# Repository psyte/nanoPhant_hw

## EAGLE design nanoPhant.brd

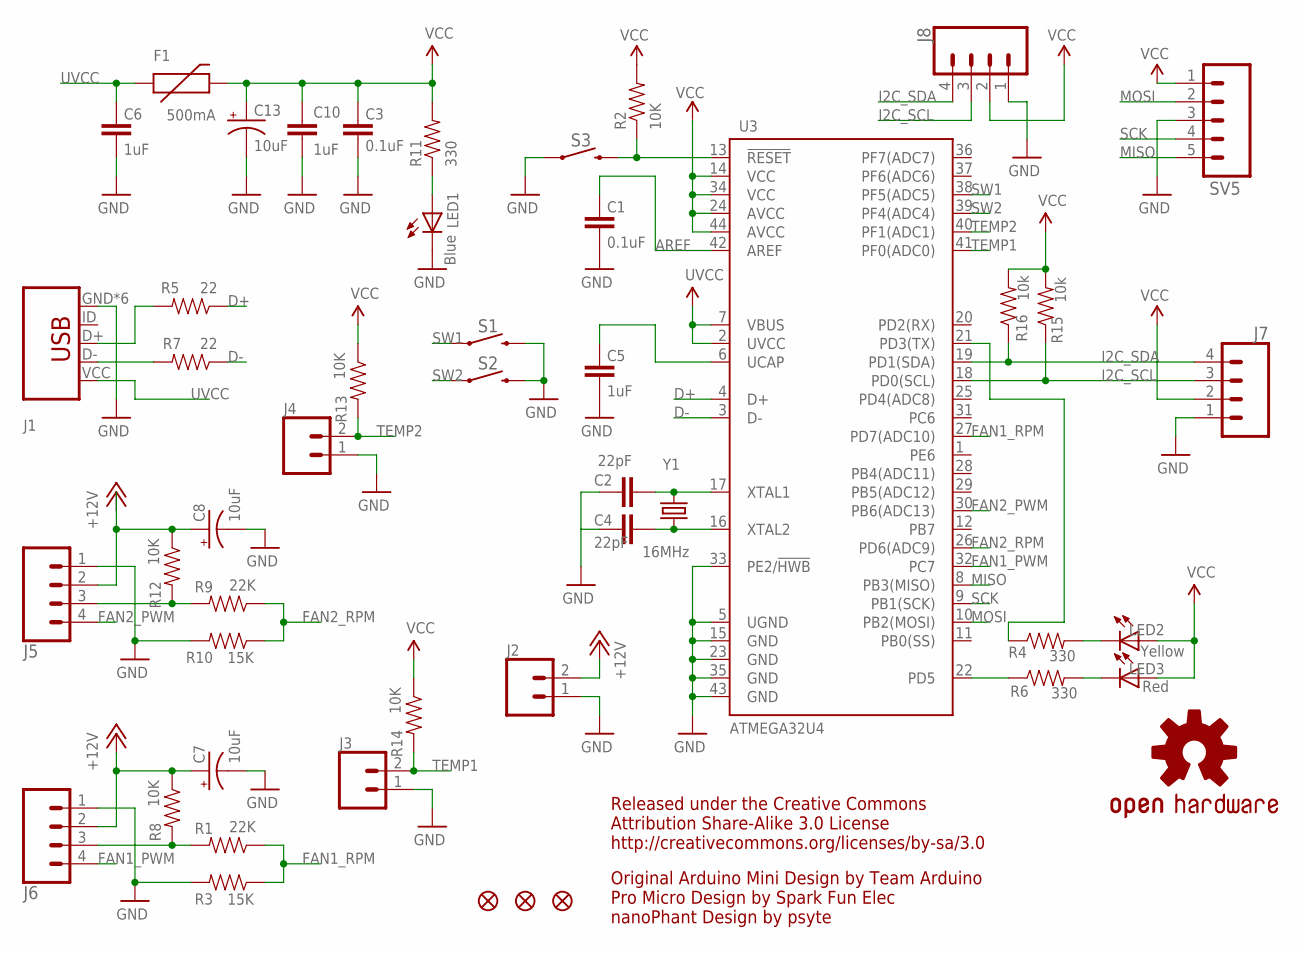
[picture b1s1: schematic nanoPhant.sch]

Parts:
C1, C3: 0.1uF; C0603
C2, C4: 22pF; C0603
C5, C6, C10: 1uF; C0603
C7, C8, C13: 10uF; EIA3216
F1: 500mA; PTC-1206
FD1, FD2, FD3: FIDUCIAL1X2; FIDUCIAL-1X2
J1: AMP FCI 10103594-0001LF; MICRO_USB_4_LEGS
J2, J3, J4: CONN_02; 1X02
J5, J6, J7, J8: CONN_04; 1X04
LED1: Blue; LED-0603
LED2: Yellow; LED-0603
LED3: Red; LED-0603
R1, R9: 22K; 0603-RES
R2, R8, R12, R13, R14: 10K; 0603-RES
R3, R10: 15K; 0603-RES
R4, R6, R11: 330; 0603-RES
R5, R7: 22; 0603-RES
R15, R16: 10k; 0603-RES
S1, S2, S3: MOMENTARY-SWITCH-SPST-SMD-6.0X3.5MM; TACTILE_SWITCH_SMD_6.0X3.5MM
SV5: CONN_05; 1X05
U3: ATMEGA32U4; QFN-44-NOPAD_1:1-OUTFAKES
U$3: OSHW-LOGOS; OSHW-LOGO-S
Y1: 16MHz; CRYSTAL-SMD-5X3

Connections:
+12V: C7.A (+), C8.A (+), J2.2, J5.2, J6.2, R8.1, R12.1
AREF: C1.2, U3.42 (AREF)
D+: R5.1, U3.4 (D+)
D-: R7.1, U3.3 (D-)
FAN1_PWM: J6.4, U3.32 (PC7)
FAN1_RPM: R1.1, R3.1, U3.27 (PD7(ADC10))
FAN2_PWM: J5.4, U3.30 (PB6(ADC13))
FAN2_RPM: R9.1, R10.1, U3.26 (PD6(ADC9))
GND: C1.1, C2.2, C3.1, C4.2, C5.1, C6.1, C7.C (-), C8.C (-), C10.2, C13.C (-), J1.GND, J1.P$1 (GND), J1.P$2 (GND), J1.P$3 (GND), J1.P$4 (GND), J1.P$5 (GND), J2.1, J3.1, J4.1, J5.1, J6.1, J7.1, J8.1, LED1.C, R3.2, R10.2, S1.2, S2.2, S3.1, SV5.3, U3.5 (UGND), U3.15 (GND), U3.23 (GND), U3.33 (PE2/!HWB), U3.35 (GND), U3.43 (GND)
I2C_SCL: J7.3, J8.3, R15.1, U3.18 (PD0(SCL))
I2C_SDA: J7.4, J8.4, R16.1, U3.19 (PD1(SDA))
MISO: SV5.5, U3.8 (PB3(MISO))
MOSI: SV5.2, U3.10 (PB2(MOSI))
unnamed: C4.1, U3.16 (XTAL2), Y1.1
unnamed: C2.1, U3.17 (XTAL1), Y1.3 (2)
unnamed: R4.1, U3.21 (PD3(TX))
unnamed: C5.2, U3.6 (UCAP)
unnamed: LED2.C, R4.2
unnamed: J1.D-, R7.2
unnamed: LED3.C, R6.2
unnamed: J1.D+, R5.2
unnamed: J6.3, R1.2, R8.2
unnamed: J5.3, R9.2, R12.2
unnamed: LED1.A, R11.1
RESET: R2.1, S3.2, U3.13 (!RESET)
SCK: SV5.4, U3.9 (PB1(SCK))
SW1: S1.1, U3.38 (PF5(ADC5))
SW2: S2.1, U3.39 (PF4(ADC4))
TEMP1: J3.2, R14.2, U3.41 (PF0(ADC0))
TEMP2: J4.2, R13.2, U3.40 (PF1(ADC1))
TXLED: R6.1, U3.22 (PD5)
UVCC: C6.2, F1.1, J1.VCC (VBUS), U3.2 (UVCC), U3.7 (VBUS)
VCC: C3.2, C10.1, C13.A (+), F1.2, J7.2, J8.2, LED2.A, LED3.A, R2.2, R11.2, R13.1, R14.1, R15.2, R16.2, SV5.1, U3.14 (VCC), U3.24 (AVCC), U3.34 (VCC), U3.44 (AVCC)

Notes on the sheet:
Original Arduino Mini Design by Team Arduino Pro Micro Design by Spark Fun Elec nanoPhant Design by psyte
Released under the Creative Commons Attribution Share-Alike 3.0 License http://creativecommons.org/licenses/by-sa/3.0

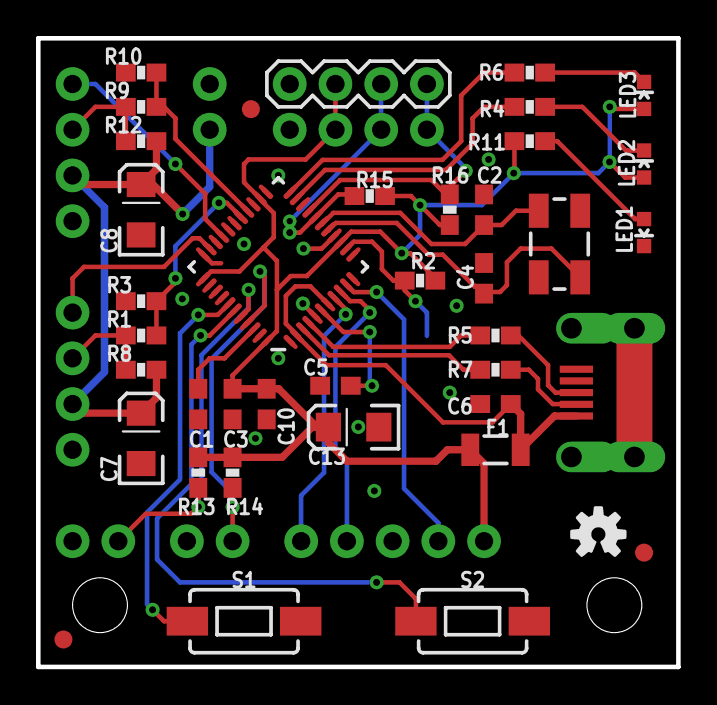
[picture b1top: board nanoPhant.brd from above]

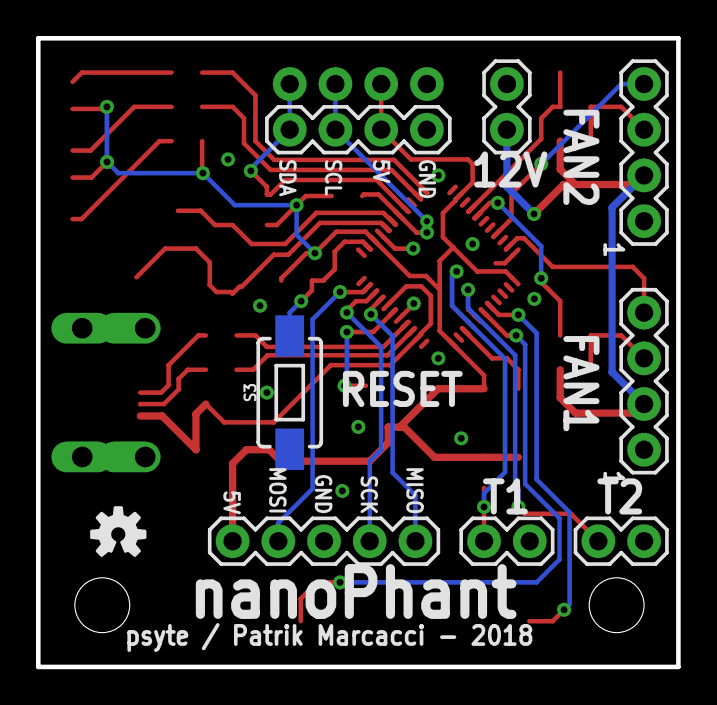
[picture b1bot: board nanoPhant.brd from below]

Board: 2 copper layers, 35.6 x 34.9 mm, 49 parts (9 on the bottom side), 33 nets.

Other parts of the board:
U$1: OSHW-LOGOS; OSHW-LOGO-S

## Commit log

2018-12-20 Layout done
2018-12-24 Routed and Gerber files
2018-12-28 Final version
    Updated USB footprint, fiducials, images, etc

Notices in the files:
parts and their libraries:
SparkFun-Connectors: Licensing: Creative Commons ShareAlike 4.0 International - https://creativecommons.org/licenses/by-sa/4.0
